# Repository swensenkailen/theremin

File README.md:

# theremin
Development repo for embedded Arduino theremin project by Kailen Swensen and Will McDonald

A wiring diagram is provided in the [build documentation](/docs/README.md)

### Enclosure
[enclosure documentation](/enclosure/README.md)

### Sensor Test
[test documentation](/sensor-test/README.md)

### Button Test
[test documentation](/button-test/README.md)

### Audio Output Test
[test documentation](/audio-out-test/README.md)

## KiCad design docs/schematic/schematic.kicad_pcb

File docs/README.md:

A KiCad project is included, containing the used wiring diagram, and a proposed PCB design.

## Wiring Diagram:

The Raspberry Pi Pico symbols footprints were sourced from [this repo](https://github.com/ncarandini/KiCad-RP-Pico/).  No modifications were made.

License [here](https://github.com/ncarandini/KiCad-RP-Pico/blob/dc6f9b9f213dc36eebce626aa9ee72a333fa0db3/LICENSE)

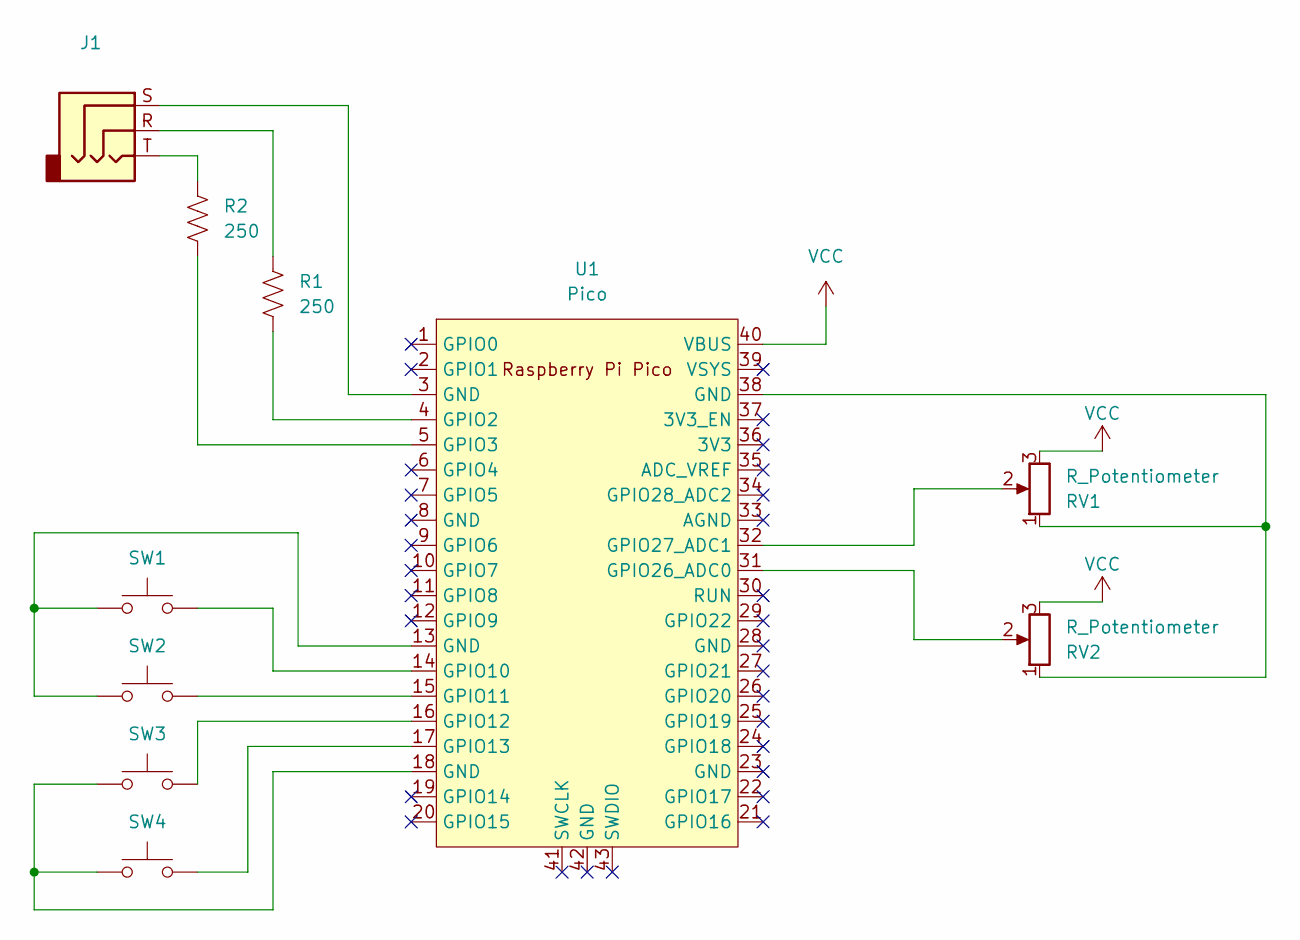
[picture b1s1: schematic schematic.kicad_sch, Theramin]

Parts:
J1: (no value)
R1, R2: 250; R_Axial_DIN0309_L9.0mm_D3.2mm_P15.24mm_Horizontal
RV1, RV2: R_Potentiometer; SolderWire-0.5sqmm_1x03_P4.6mm_D0.9mm_OD2.1mm
SW1, SW2, SW3, SW4: SW_Push; SolderWire-0.15sqmm_1x02_P4mm_D0.5mm_OD1.5mm
U1: Pico; RPi_Pico_SMD_TH

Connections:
unnamed: J1.R, R1.1
unnamed: J1.S, U1.3 (GND)
unnamed: J1.T, R2.1
unnamed: R1.2, U1.4 (GPIO2)
unnamed: R2.2, U1.5 (GPIO3)
unnamed: RV1.1, RV2.1, U1.38 (GND)
unnamed: RV1.2, U1.32 (GPIO27_ADC1)
unnamed: RV2.2, U1.31 (GPIO26_ADC0)
unnamed: SW1.1, SW2.1, U1.13 (GND)
unnamed: SW1.2, U1.14 (GPIO10)
unnamed: SW2.2, U1.15 (GPIO11)
unnamed: SW3.1, SW4.1, U1.18 (GND)
unnamed: SW3.2, U1.16 (GPIO12)
unnamed: SW4.2, U1.17 (GPIO13)
VCC: RV1.3, RV2.3, U1.40 (VBUS)

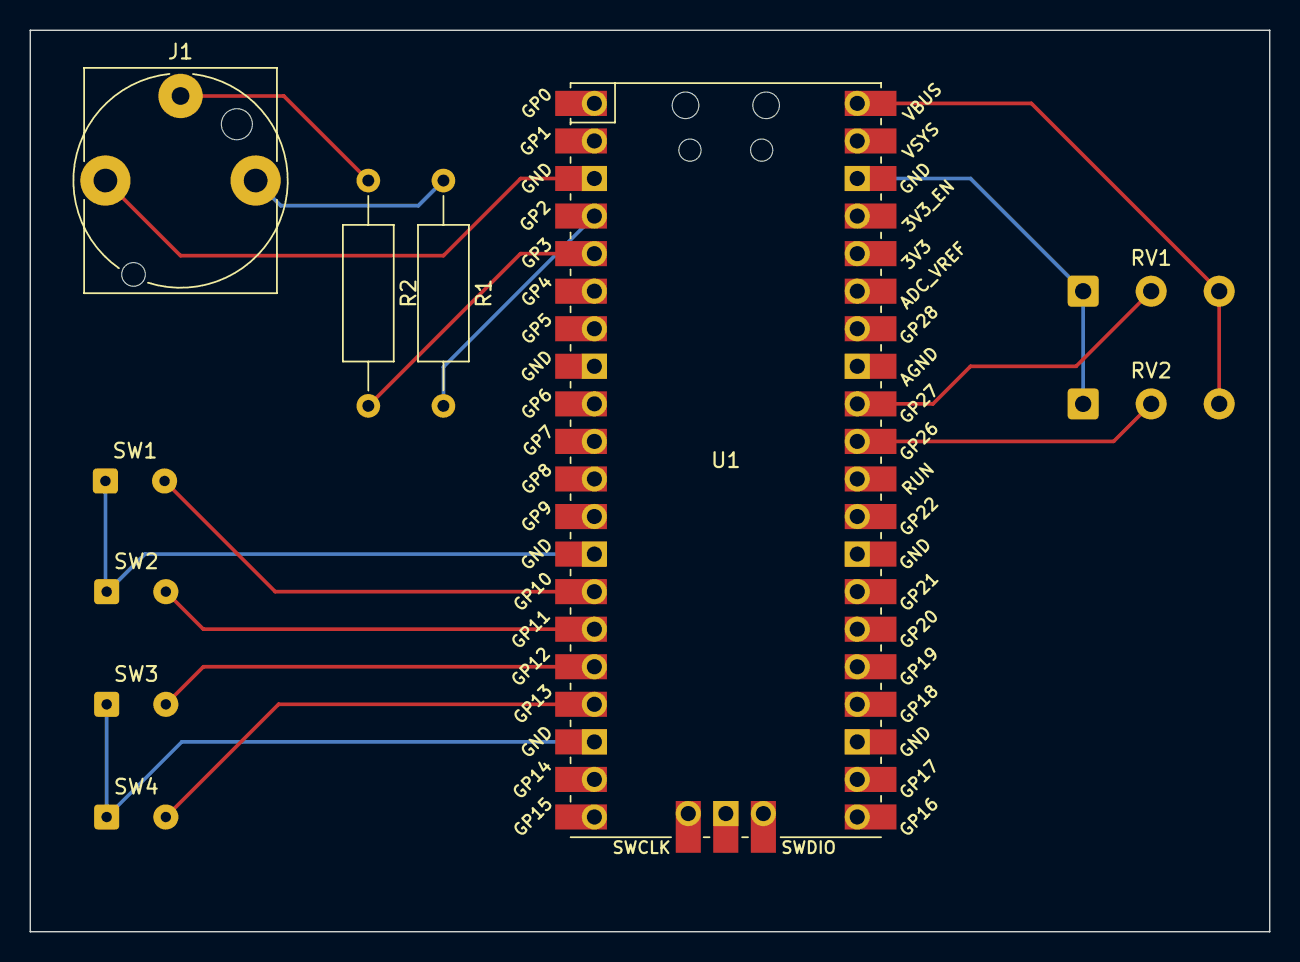
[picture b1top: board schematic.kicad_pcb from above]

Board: 2 copper layers, 83.8 x 61.0 mm, 10 parts (0 on the bottom side), 15 nets.

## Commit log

2022-04-27 Added first file
2022-04-30 Modelled a bracket for the USB port
    Created a bracket to support the USB type B panel mount to USB micro B adapter cable. Will be 3d printed to use in cardboard box prototype enclosure.
2022-05-01 KiCad project
    Added KiCad Project with wiring diagram and PCB design for theramin.
    Included License for used KiCad libraries.
2022-05-01 Update README
    Added link to docs/README to README
2022-05-01 Button bracket for cardboard prototype
    Modeled brackets to support 16mm momentary pushbuttons in a carboard enclosure.
2022-05-01 Updated USB panel mount for screw fitment
    When printed, the fitment of the bracket was too tight on the screws. I have adjusted the freecad document and updated the files for a better fit.
2022-05-01 Updated Enclosure README, added images
    Explained the current situation regarding the enclosure, and included schematic images from FreeCad
2022-05-02 Updated arduino c++ file
    Added template i/o code for the arduino board
2022-05-05 Sensor Data Collection Test
    Successfully proved the ability to collect calibrated data from one sensor.
    Remapped ADC data to voltage, then from voltage to distance in cm.
    Change in distance will now be able to be represented linearly.
2022-05-05 Sensor Test Documentation
    Documented purpose, methods, learning of test
2022-05-05 Update README.md
    Updated Main README to link to extended documentation
2022-05-19 Button test
    Tests functionality of 4 attached buttons on prototype theremin
2022-05-19 Create README.md
    Created README including library used
2022-05-19 Update Schematic to as built
    We deviated from the original schematic as it was simpler to construct/ source in the way we built it.
2022-05-20 Configured build caching
    Configured caching for VSCode Arduino extension to reduce build time.
2022-05-20 First Pass of IrDistanceSensor Class
    Implemented a class to simplify implementation of sensor data use.
    Sensor calibration can be configured using `#define`'s. Default configuration is for Sharp GP2Y0A21YK0F IR Sensors.
    I do not have hardware on hand, so this has yet to be tested. It is written based on my successfully tested `sensor-test`.
2022-05-20 Added test for audio output
    Test for audio output using a sweeping frequency
2022-05-20 Created README for audio-out-test
2022-05-20 Updated README
    added BOM for button-test
2022-05-20 Implemented IrDistanceSensor_Relative
    New derived class provides 0..1 range for distance, to be configured at runtime by calling SetLow and SetHigh.
    this has not been tested on hardware as I don't have it on hand.
2022-05-20 Update IrDistanceSensor.h
    Corrected Clamping
2022-05-29 Added Tonesynth class
    Class that uses tone() functionality to act as a synth/tone generator, or for our purposes, a theremin.
2022-05-29 Updated theremin
    Updated theremin using Tonesynth class
2022-05-30 Added Buttons class
    More compact version of Button class used in button-test, made for a circuit with four buttons and defaulted to fit our prototype model.
2022-05-30 Updated readme
    Added links to button and audio output test documentation
2022-05-30 Update audio-out-test.ino
    Updated output pin and increased tone duration
2022-05-30 Update Schematic
    We found that the tone() function can only service one pin at a time, and that we can tie the t and r of the audio output together with no ill effects.
2022-05-30 Updated theremin configuration based on testing
2022-05-30 Better defaults for IrDistanceSensor_Relative
2022-05-30 Corrected Calibration of IrDistanceSensor_Relative
2022-05-30 Corrected Pin labels, logging
2022-07-26 New branch to test daisy
    Contains most of the implementation code for the theremin using Daisy hardware and libraries
